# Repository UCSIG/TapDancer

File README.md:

<div align="center">
  
</div>

<h1 align="center">TapDancer</h1>

<p align="center">
  A three-button Bluetooth LE footswitch for musicians. It turns pages in sheet-music apps, sends media keys and triggers keyboard shortcuts, so both hands stay on the instrument.
</p>

<p align="center">

</p>

<div align="center">
  <table>
    <tr>
      <td></td>
      <td></td>
    </tr>
    <tr>
      <td></td>
      <td></td>
    </tr>
  </table>
</div>

## Contents

- [Contents](#contents)
- [Overview](#overview)
- [Features](#features)
- [Specifications](#specifications)
- [Repository layout](#repository-layout)
- [Hardware](#hardware)
- [Firmware](#firmware)
  - [Building and flashing](#building-and-flashing)
- [Companion app](#companion-app)
  - [Building the app](#building-the-app)
- [Release builds](#release-builds)
- [Assembly](#assembly)
- [Configuration protocol](#configuration-protocol)
- [Contributing](#contributing)
- [License](#license)

## Overview

TapDancer is an open-source footswitch based on the [Seeed Studio XIAO nRF52840](https://wiki.seeedstudio.com/XIAO_BLE/). It pairs with phones, tablets and computers as a standard BLE HID keyboard, so it works with any application that accepts keyboard or media keys: sheet-music readers, DAWs, presentation software, lyric prompters and so on.

Each of the three buttons recognizes single, double, triple and long presses, and every gesture can be mapped to a key using the companion app. Up to 16 configurations are stored on the device, so no phone is needed once the pedal is set up.

The PCB sits inside an off-the-shelf Roland DP-2 sustain pedal. The repository contains everything needed to build one: the KiCad project, 3D-printable mounting parts, the PlatformIO firmware and the Flutter app.

## Features

- Three footswitches, each with four configurable gestures (single, double, triple and long press)
- Any key, modifier combination or consumer/media key can be assigned to a gesture
- 16 configurations stored on the device; optionally selectable in hardware with jumpers (R2R DAC)
- Up to four simultaneous host connections
- Standard BLE pairing and bonding
- Three LEDs for battery level, configuration changes and the auto-off countdown
- Configurable auto-off after inactivity (10 minutes by default)
- Around 370 hours of connected runtime on a 1200 mAh cell; 0.16 µA when off
- Companion app for Android, iOS, Windows, macOS and Linux

## Specifications

| | |
| --- | --- |
| MCU | Nordic nRF52840 (Seeed XIAO nRF52840) |
| Connectivity | Bluetooth LE, HID keyboard and consumer control |
| Buttons | 3, with 4 gestures each |
| Stored configurations | 16 |
| Simultaneous connections | Up to 4 |
| Battery | Li-ion / LiPo, approx. 1200 mAh typical |
| Current draw | 3.2 mA connected, 10 mA advertising, 0.16 µA off |
| Connected runtime | Approx. 370 h at 1200 mAh |
| Auto-off | Configurable, 10 min default |
| Hardware revision | v1.0.0 |

Power measurements and the R2R DAC calculations are in [`pcb/tapdancer_v1.0/measurements/`](pcb/tapdancer_v1.0/measurements/).

## Repository layout

```text
app/            Flutter companion app (Android, iOS, Windows, macOS, Linux)
firmware/       PlatformIO firmware for the XIAO nRF52840, patched bootloader
pcb/            KiCad project, Gerbers, BOM and plots (tapdancer_v1.0)
mechanical/     3D-printable battery mount and drilling template
.github/        GitHub Actions workflow for release builds
```

## Hardware

TapDancer v1.0 is a four-layer PCB designed in KiCad. Its outline fits inside a [Roland DP-2](https://www.roland.com/global/products/dp-2/) sustain pedal, which is inexpensive, robust and easy to find. Schematic, layout, footprints, Gerbers and BOM are in [`pcb/tapdancer_v1.0/`](pcb/tapdancer_v1.0/).

| Block | Part / notes |
| --- | --- |
| MCU / BLE | Seeed Studio XIAO nRF52840 (nRF52840, Cortex-M4F, BLE 5) |
| Enclosure | Roland DP-2 sustain pedal |
| Buttons | 3 footswitches (primary, secondary, tertiary) |
| Indicators | 3 LEDs (battery, config, status) |
| Battery | 1200 mAh LiPo cell |
| Power | TP4056 charger, LDS3985 LDO, software-controlled power enable and battery voltage divider |
| Configuration select | R2R DAC and jumpers, producing 16 discrete ADC levels |
| Connectors | 3.5 mm jack (PJ392A), Roland DP-2 sustain-pedal footprint |

Fabrication outputs (e.g. for JLCPCB):

- Gerbers: [`pcb/tapdancer_v1.0/outputs/gerber/`](pcb/tapdancer_v1.0/outputs/gerber/)
- Interactive BOM: [`outputs/bom/bom_tapdancer_v1.0.html`](pcb/tapdancer_v1.0/outputs/bom/bom_tapdancer_v1.0.html)
- Schematic PDF: [`outputs/schematic/tapdancer_v1.0.pdf`](pcb/tapdancer_v1.0/outputs/schematic/tapdancer_v1.0.pdf)

References: [nRF52840 Product Specification](https://docs.nordicsemi.com/bundle/ps_nrf52840/page/keyfeatures_html5.html), [Seeed XIAO nRF52840 wiki](https://wiki.seeedstudio.com/XIAO_BLE/), [USB HID Usage Tables](https://usb.org/document-library/hid-usage-tables-15).

## Firmware

The firmware is a PlatformIO project using the Arduino framework on the Adafruit nRF52 core.

- Board `xiaoble_adafruit`, SoftDevice S140 v7.3.0
- Configurations stored in LittleFS on internal flash (approx. 28 kB)
- BLE services: HID keyboard and consumer control, Battery Service, Nordic UART Service (configuration)

The device requires a patched Adafruit nRF52 bootloader (0.9.2 with one fix that makes BLE OTA updates work). The patch and prebuilt binaries are in [`firmware/bootloader/`](firmware/bootloader/).

### Building and flashing

```bash
git clone https://github.com/UCSIG/TapDancer.git
cd TapDancer/firmware

pio run                 # build
pio run -t upload       # flash via nrfutil (default upload protocol)
pio device monitor      # serial console, 115200 baud
```

A new board needs the bootloader flashed first. See [`firmware/bootloader/README.md`](firmware/bootloader/README.md) and the notes at the top of [`firmware/platformio.ini`](firmware/platformio.ini).

## Companion app

The app is used to pair devices, edit configurations and update firmware.

<table>
  <tr>
    <td align="center"><b>Two simultaneous devices</b></td>
    <td align="center"><b>Button configurations</b></td>
    <td align="center"><b>Settings</b></td>
  </tr>
  <tr>
    <td></td>
    <td></td>
    <td></td>
  </tr>
</table>

With the app you can:

- Scan for, pair and connect to one or more TapDancers
- Assign a key (with modifiers) or media key to each gesture
- Name, reset and delete the 16 configuration slots
- Adjust double-click and long-press timing per button. A double-click time of `0` enables direct mode, where a press fires immediately.
- Change device settings: auto-off timeout, maximum number of connections, identify (blink) and factory reset
- Export and import configurations as `.tdcfg` files, either a single configuration or all 16 at once
- Restore earlier configurations from automatic backups. The app saves a backup of the device's configurations each time it connects (the last 20 per device), so an accidental overwrite can be undone.
- Update the firmware over BLE with the firmware bundled in the app (Android, iOS and macOS)

The app is written in Flutter and uses [`universal_ble`](https://pub.dev/packages/universal_ble) for Bluetooth on all platforms.

### Building the app

Requires Flutter 3.

```bash
cd app
flutter pub get

flutter run                # run on a connected device or desktop

flutter build apk          # Android
flutter build ipa          # iOS
flutter build windows      # Windows
flutter build macos        # macOS
flutter build linux        # Linux
```

Bluetooth permissions and entitlements are already configured in the platform projects.

The app bundles a firmware package for OTA updates in [`app/assets/firmware/`](app/assets/firmware/). After changing the firmware, run [`app/scripts/sync_firmware.ps1`](app/scripts/sync_firmware.ps1) to rebuild it and copy it into the app. [`app/scripts/build_release.ps1`](app/scripts/build_release.ps1) does this and then builds the Android and Windows release files locally.

## Release builds

The [Build](.github/workflows/release.yml) workflow builds the firmware, the Android APK and the Windows app on GitHub Actions. The firmware is built first and bundled into both apps, so each release ships with matching firmware.

- **Manual run:** Actions → Build → Run workflow. The results are available as workflow artifacts.
- **Release:** push a tag that matches the app version in [`app/pubspec.yaml`](app/pubspec.yaml), for example:

  ```bash
  git tag v1.2.0
  git push origin v1.2.0
  ```

  The workflow then creates a draft release containing the APK, the Windows zip and the firmware as `.zip` (DFU), `.hex` and `.uf2`. Review the draft and publish it.

## Assembly

1. Get a Roland DP-2 sustain pedal to use as the enclosure.
2. Order the PCB using the Gerbers in [`pcb/tapdancer_v1.0/outputs/gerber/`](pcb/tapdancer_v1.0/outputs/gerber/), either bare or assembled. The [interactive BOM](pcb/tapdancer_v1.0/outputs/bom/bom_tapdancer_v1.0.html) helps with placement.
3. Solder the XIAO nRF52840, footswitches, LEDs, battery protection and connectors.
4. 3D print the battery mount from [`mechanical/`](mechanical/), which holds the cell inside the housing:
   - `TapDancer v1.0 LiPo Plate.stl`
   - `TapDancer v1.0 LiPo Cover.stl`
5. Drill the housing for the LEDs and buttons using `mechanical/TapDancer v1.0 Drilling Template.pdf`.
6. Flash the bootloader and firmware (see [Firmware](#firmware)).
7. Mount the PCB in the pedal and set it up with the [companion app](#companion-app).

> [!WARNING]
> Check the polarity of the battery plug before connecting it. Many cells are sold with reversed JST polarity. Compare against the silkscreen and re-pin the connector if necessary.

## Configuration protocol

Once paired, the pedal sends standard HID reports, so the host treats it like any Bluetooth keyboard. Each gesture maps to either a keyboard report (modifiers plus key codes) or a consumer control code.

The active configuration is selected from the app or, if jumpers are fitted, by the R2R DAC: the firmware reads the ADC voltage and picks one of 16 configurations by threshold. Battery voltage is measured through a divider, reported via the BLE Battery Service and shown on the LEDs at startup.

The app communicates with the device over the Nordic UART Service using a short, CRC-checked command format (`G#…` get, `S#…` set, `P#…` push). The implementation is in [`app/lib/utils/ble_command.dart`](app/lib/utils/ble_command.dart) and [`firmware/src/command.h`](firmware/src/command.h).

## Contributing

Issues and pull requests are welcome. For larger changes, please open an issue first.

- The command protocol is shared between firmware and app. Keep [`firmware/src/settings.h`](firmware/src/settings.h) and [`app/lib/models/device_settings.dart`](app/lib/models/device_settings.dart) in sync.
- Record changes in [`CHANGELOG.md`](CHANGELOG.md) following [Keep a Changelog](https://keepachangelog.com/) and [Semantic Versioning](https://semver.org/).

## License

| Part | License |
| --- | --- |
| Firmware ([`firmware/`](firmware/)) and app ([`app/`](app/)) | [MIT](LICENSE) |
| PCB ([`pcb/`](pcb/)) and enclosure parts ([`mechanical/`](mechanical/)) | [CERN-OHL-P-2.0](LICENSE-HARDWARE) |

---

<sub>Designed and built by UCSIG. Developed since 2024.</sub>

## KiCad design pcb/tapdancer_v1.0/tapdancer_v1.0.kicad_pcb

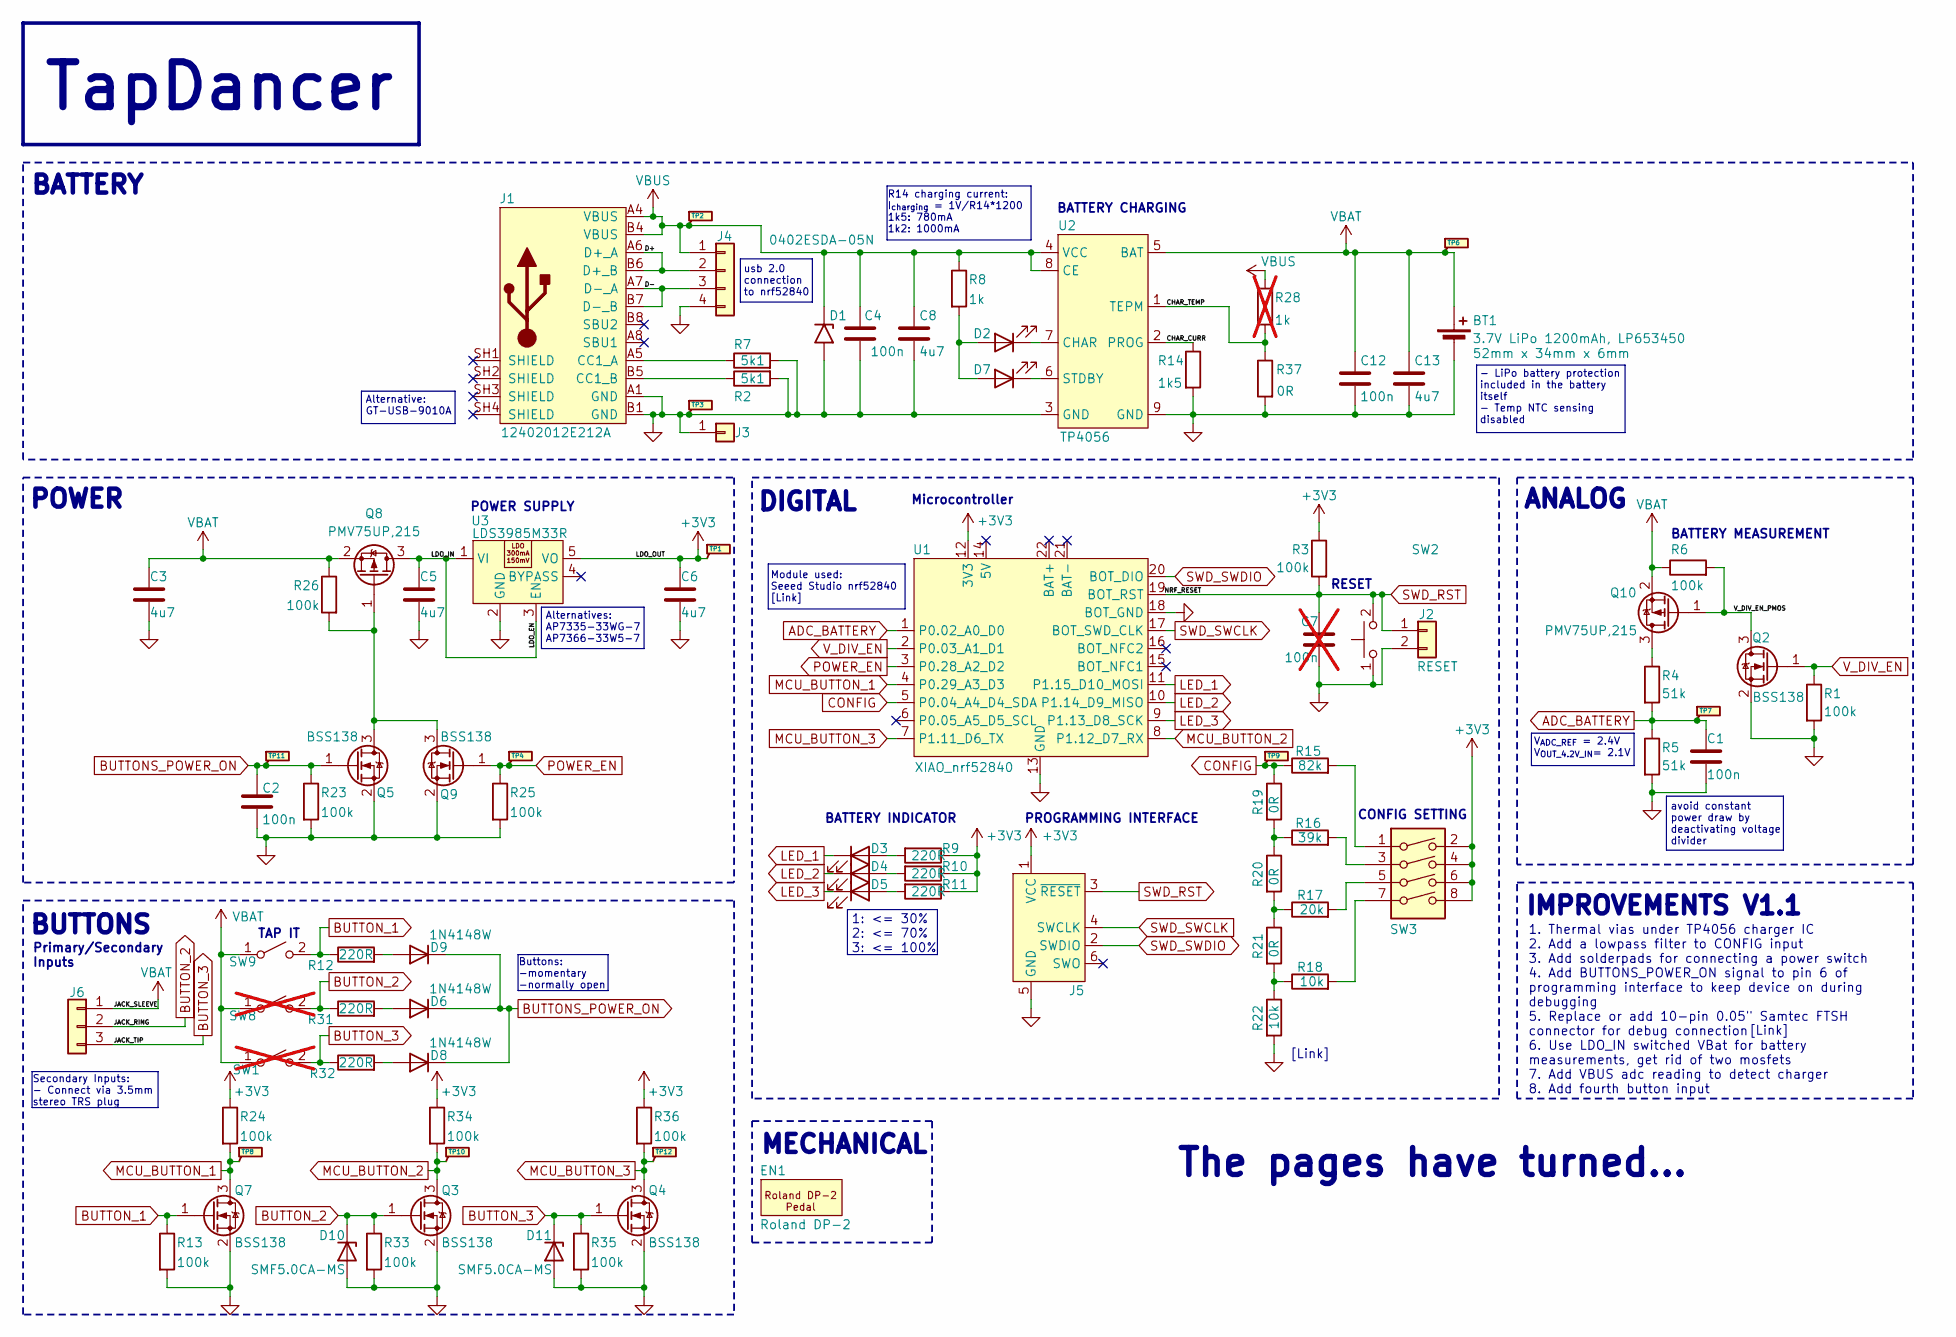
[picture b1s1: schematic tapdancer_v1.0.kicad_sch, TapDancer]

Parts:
BT1: 3.7V LiPo 1200mAh, LP653450; JST_PH_B2B-PH-K_1x02_P2.00mm_Vertical; LCSC Part Number C131337
C1: 100n; C_0603_1608Metric_Pad1.08x0.95mm_HandSolder; Manufacturer Part Number TS170R1H104MSBFB0R; LCSC Part Number C282519
C2: 100n; C_0603_1608Metric_Pad1.08x0.95mm_HandSolder; LCSC Part Number C282519
C3, C5, C6: 4u7; C_0603_1608Metric_Pad1.08x0.95mm_HandSolder; LCSC Part Number C18185770
C4, C12: 100n; C_0603_1608Metric_Pad1.08x0.95mm_HandSolder; Voltage 10V; LCSC Part Number C282519
C7: 100n; C_0603_1608Metric_Pad1.08x0.95mm_HandSolder; LCSC Part Number C282519; not fitted
C8, C13: 4u7; C_0603_1608Metric_Pad1.08x0.95mm_HandSolder; Voltage 10V; LCSC Part Number C2959727
D1: 0402ESDA-05N; D_0402_1005Metric; LCSC Part Number C316049
D2: LEDR; PinHeader_1x02_P2.54mm_Vertical
D3, D4, D5, D7: LEDG; PinHeader_1x02_P2.54mm_Vertical
D6, D8, D9: 1N4148W; D_SOD-123; LCSC Part Number C2099
D10, D11: SMF5.0CA-MS; D_SOD-123; LCSC Part Number C7473196
EN1: Roland DP-2; Roland_DP-2
J1: 12402012E212A; LCSC Part Number 12402012E212A
J2: Conn_01x02; PinHeader_1x02_P2.54mm_Vertical
J3: Conn_01x01; PinHeader_1x01_P2.54mm_Vertical
J4: Conn_01x04; PinHeader_1x04_P2.54mm_Vertical
J5: Conn_ARM_SWD_TagConnect_TC2030-NL; Tag-Connect_TC2030-IDC-NL_2x03_P1.27mm_Vertical
J6: Conn_01x03; PinHeader_1x03_P2.54mm_Vertical
Q2, Q3, Q4, Q5, Q7, Q9: BSS138; TSOT-23; LCSC Part Number C5224266
Q8, Q10: PMV75UP,215; TSOT-23; LCSC Part Number C461153
R1, R3, R6, R13, R23, R24, R25, R26, R33, R34, R35, R36: 100k; R_0603_1608Metric_Pad0.98x0.95mm_HandSolder; LCSC Part Number C14675
R2, R7: 5k1; R_0603_1608Metric_Pad0.98x0.95mm_HandSolder; LCSC Part Number C2907044
R4: 51k; R_0603_1608Metric_Pad0.98x0.95mm_HandSolder; LCSC Part Number C14675
R5: 51k; R_0603_1608Metric_Pad0.98x0.95mm_HandSolder; LCSC Part Number C2907049
R8: 1k; R_0603_1608Metric_Pad0.98x0.95mm_HandSolder; LCSC Part Number C112433
R9, R10, R11, R12, R31, R32: 220R; R_0603_1608Metric_Pad0.98x0.95mm_HandSolder; LCSC Part Number C2907014
R14: 1k5; R_0603_1608Metric_Pad0.98x0.95mm_HandSolder; LCSC Part Number C3016293
R15: 82k; R_0603_1608Metric_Pad0.98x0.95mm_HandSolder; LCSC Part Number C3016293
R16: 39k; R_0603_1608Metric_Pad0.98x0.95mm_HandSolder; LCSC Part Number C3016293
R17: 20k; R_0603_1608Metric_Pad0.98x0.95mm_HandSolder; LCSC Part Number C3016293
R18, R22: 10k; R_0603_1608Metric_Pad0.98x0.95mm_HandSolder; LCSC Part Number C3016293
R19, R20, R21, R37: 0R; R_0603_1608Metric_Pad0.98x0.95mm_HandSolder; LCSC Part Number C103199
R28: 1k; R_0603_1608Metric_Pad0.98x0.95mm_HandSolder; LCSC Part Number C112433; not fitted
SW1, SW8: FOOTSWITCH; not fitted
SW2: RESET; SW_Push
SW3: SW_DIP_x04; PinHeader_2x04_P2.54mm_Vertical
SW9: FOOTSWITCH; SolderWire-0.5sqmm_1x02_P4.8mm_D0.9mm_OD2.3mm
TP1: +3V3; ViaOszi_TestPoint
TP2: VBUS; ViaOszi_TestPoint
TP3: GND; ViaOszi_TestPoint
TP4: POWER_EN; ViaOszi_TestPoint
TP6: VBAT; ViaOszi_TestPoint
TP7: ADC_BATTERY; ViaOszi_TestPoint
TP8: MCU_BUTTON_1; ViaOszi_TestPoint
TP9: CONFIG; ViaOszi_TestPoint
TP10: MCU_BUTTON_2; ViaOszi_TestPoint
TP11: BUTTONS_ON; ViaOszi_TestPoint
TP12: MCU_BUTTON_3; ViaOszi_TestPoint
U1: XIAO_nrf52840
U2: TP4056; HSOP-8-1EP_3.9x4.9mm_P1.27mm_EP2.41x3.1mm; LCSC Part Number C20199357
U3: LDS3985M33R; SOT-23-5_HandSoldering; LCSC Part Number C222381

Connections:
+3V3: C6.1, J5.1 (VCC), R3.1, R9.1, R10.1, R11.1, R24.1, R34.1, R36.1, SW3.2, SW3.4, SW3.6, SW3.8, TP1.1, U1.12 (3V3), U3.5 (VO)
/CHAR_CURR: R14.1, U2.2 (PROG)
/CHAR_TEMP: R28.2, R37.1, U2.1 (TEPM)
/D+: J1.A6 (D+_A), J1.B6 (D+_B), J4.2
/D-: J1.A7 (D-_A), J1.B7 (D-_B), J4.3
/LDO_EN: C5.1, Q8.3 (D), U3.1 (VI), U3.3 (EN)
/V_DIV_EN_PMOS: Q2.3 (D), Q10.1 (G), R6.2
ADC_BATTERY: C1.1, R4.2, R5.1, TP7.1, U1.1 (P0.02_A0_D0)
BUTTONS_POWER_ON: C2.1, D6.1 (K), D8.1 (K), D9.1 (K), Q5.1 (G), R23.1, TP11.1
BUTTON_1: Q7.1 (G), R12.1, R13.1, SW9.2 (B)
BUTTON_2: D10.1 (K), J6.2, Q3.1 (G), R31.1, R33.1, SW8.2 (B)
BUTTON_3: D11.1 (K), J6.3, Q4.1 (G), R32.1, R35.1, SW1.2 (B)
CONFIG: R15.1, R19.1, TP9.1, U1.5 (P0.04_A4_D4_SDA)
GND: BT1.2 (-), C1.2, C2.2, C3.2, C4.1, C5.2, C6.2, C7.2, C8.2, C12.2, C13.2, D1.2 (A2), D10.2 (A), D11.2 (A), J1.A1 (GND), J1.B1 (GND), J2.2, J3.1, J4.4, J5.5 (GND), Q2.2 (S), Q3.2 (S), Q4.2 (S), Q5.2 (S), Q7.2 (S), Q9.2 (S), R1.2, R2.2, R5.2, R7.2, R13.2, R14.2, R22.2, R23.2, R25.2, R33.2, R35.2, R37.2, SW2.1, TP3.1, U1.13 (GND), U1.18 (BOT_GND), U2.3 (GND), U2.9 (GND), U3.2 (GND)
LED_1: D3.1 (K), U1.11 (P1.15_D10_MOSI)
LED_2: D4.1 (K), U1.10 (P1.14_D9_MISO)
LED_3: D5.1 (K), U1.9 (P1.13_D8_SCK)
MCU_BUTTON_1: Q7.3 (D), R24.2, TP8.1, U1.4 (P0.29_A3_D3)
MCU_BUTTON_2: Q3.3 (D), R34.2, TP10.1, U1.8 (P1.12_D7_RX)
MCU_BUTTON_3: Q4.3 (D), R36.2, TP12.1, U1.7 (P1.11_D6_TX)
unnamed: D2.2 (A), D7.2 (A), R8.2
unnamed: D2.1 (K), U2.7 (CHAR)
unnamed: D3.2 (A), R9.2
unnamed: D4.2 (A), R10.2
unnamed: D5.2 (A), R11.2
unnamed: D6.2 (A), R31.2
unnamed: D7.1 (K), U2.6 (STDBY)
unnamed: D8.2 (A), R32.2
unnamed: D9.2 (A), R12.2
unnamed: J1.A5 (CC1_A), R7.1
unnamed: J1.B5 (CC1_B), R2.1
unnamed: Q5.3 (D), Q8.1 (G), Q9.3 (D), R26.2
unnamed: Q10.3 (D), R4.1
unnamed: R15.2, SW3.1
unnamed: R16.1, R19.2, R20.1
unnamed: R16.2, SW3.3
unnamed: R17.1, R20.2, R21.1
unnamed: R17.2, SW3.5
unnamed: R18.1, R21.2, R22.1
unnamed: R18.2, SW3.7
POWER_EN: Q9.1 (G), R25.1, TP4.1, U1.3 (P0.28_A2_D2)
SWD_RST: C7.1, J2.1, J5.3 (~RESET), R3.2, SW2.2, U1.19 (BOT_RST)
SWD_SWCLK: J5.4 (SWCLK), U1.17 (BOT_SWD_CLK)
SWD_SWDIO: J5.2 (SWDIO), U1.20 (BOT_DIO)
VBAT: BT1.1 (+), C3.1, C12.1, C13.1, J6.1, Q8.2 (S), Q10.2 (S), R6.1, R26.1, SW1.1 (A), SW8.1 (A), SW9.1 (A), TP6.1, U2.5 (BAT)
VBUS: C4.2, C8.1, D1.1 (A1), J1.A4 (VBUS), J1.B4 (VBUS), J4.1, R8.1, R28.1, TP2.1, U2.4 (VCC), U2.8 (CE)
V_DIV_EN: Q2.1 (G), R1.1, U1.2 (P0.03_A1_D1)

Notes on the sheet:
TAP IT
BATTERY MEASUREMENT
1: <= 30% 2: <= 70% 3: <= 100%
1. Thermal vias under TP4056 charger IC 2. Add a lowpass filter to CONFIG input 3. Add solderpads for connecting a power switch 4. Add BUTTONS_POWER_ON signal to pin 6 of programming interface to keep device on during debugging 5. Replace or add 10-pin 0.05" Samtec FTSH connector for debug connecti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
MECHANICAL
- LiPo battery protection included in the battery itself - Temp NTC sensing disabled
V_{ADC_REF} = 2.4V V_{OUT_4.2V_IN}= 2.1V
RESET
IMPROVEMENTS V1.1
TapDancer
BATTERY CHARGING
R14 charging current: I_{charging} = 1V/R14*1200 1k5: 780mA 1k2: 1000mA
[Link]
Alternative: GT-USB-9010A
Primary/Secondary Inputs
The pages have turned...
CONFIG SETTING
Microcontroller
Buttons: -momentary -normally open
DIGITAL
POWER
POWER SUPPLY
Secondary Inputs: - Connect via 3.5mm stereo TRS plug
BATTERY INDICATOR
Alternatives: AP7335-33WG-7 AP7366-33W5-7
ANALOG
BATTERY
PROGRAMMING INTERFACE
Module used: Seeed Studio nrf52840 [Link]
avoid constant power draw by deactivating voltage divider
usb 2.0 connection to nrf52840
BUTTONS

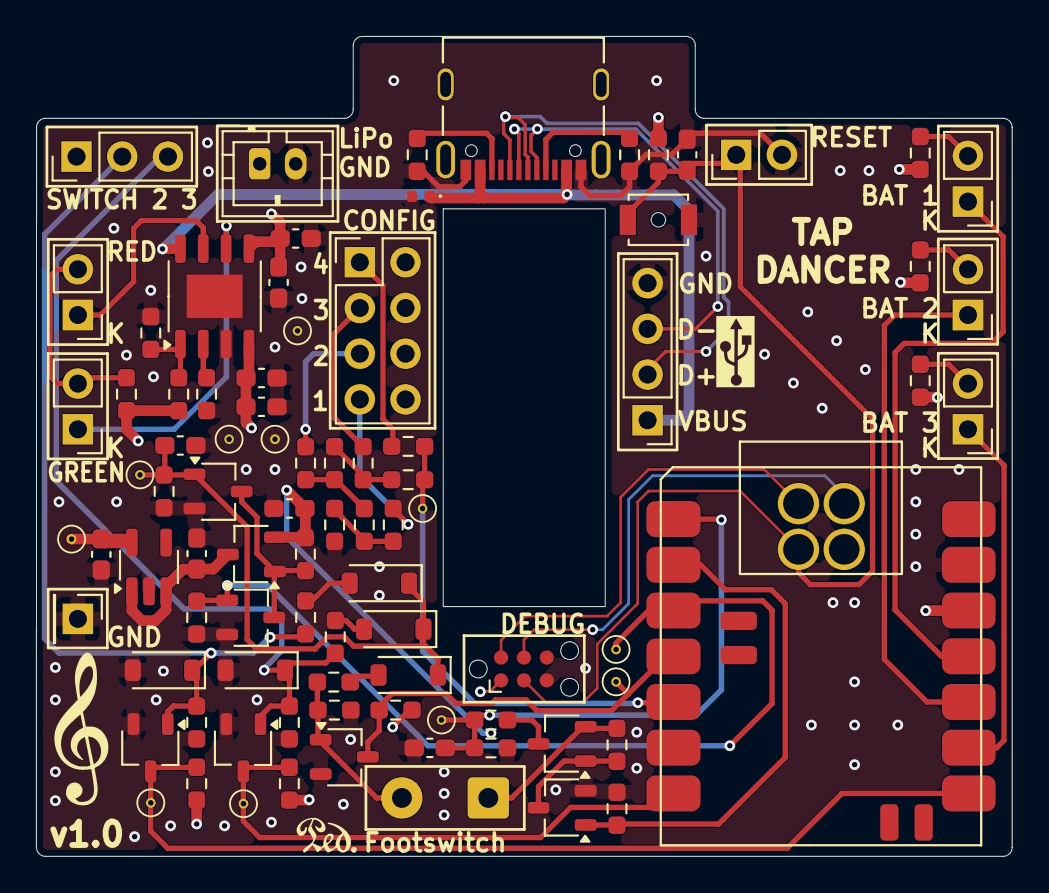
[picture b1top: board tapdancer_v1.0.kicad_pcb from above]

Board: 4 copper layers, 54.2 x 45.5 mm, 88 parts (0 on the bottom side), 47 nets.

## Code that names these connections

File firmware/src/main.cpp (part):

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static uint8_t config_cur = 0;

// Configs and mappings.
static uint8_t led_pin_mapping[LED_NUM] = {PIN_LED_1, PIN_LED_2, PIN_LED_3};
const uint16_t config_adc_thrsh_lut[16] =
    {306, 880, 1347, 1711, 2018, 2292, 2529, 2724, 2896, 3056, 3200, 3321, 3431, 3536, 3631, 4096};

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static soft_timer_t timer_autooff;

/* -------------------------------- FUNCTIONS ------------------------------- */
/* ----------------------------- GPIO AND CONFIG ---------------------------- */
static void init_gpios(void);
static uint32_t get_config_reading_adc(void);
static uint8_t get_config(uint32_t config_reading);
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    buttons[TERTIARY_BUTTON].begin(TERTIARY_BUTTON_PIN, INPUT, (TERTIARY_BUTTON_ACTIVE_LEVEL == LOW) ? true : false);

    // Power and battery.
    pinMode(PIN_POWER_EN, OUTPUT);
    pinMode(PIN_VOLT_DIV_EN, OUTPUT);
    analogReadResolution(12);

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}

static void power_enable(bool enable) {
    digitalWrite(PIN_POWER_EN, enable ? HIGH : LOW);
}

static void voltage_divider_enable(bool enable) {
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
